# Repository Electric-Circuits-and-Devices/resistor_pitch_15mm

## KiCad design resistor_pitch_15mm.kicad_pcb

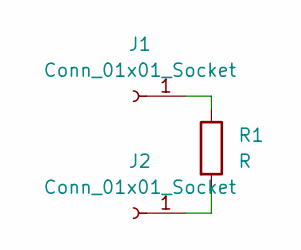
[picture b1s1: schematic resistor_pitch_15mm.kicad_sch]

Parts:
J1, J2: Conn_01x01_Socket; MountingHole_2.5mm_Pad
R1: R; R_Axial_DIN0207_L6.3mm_D2.5mm_P10.16mm_Horizontal

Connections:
unnamed: J1.1, R1.1
unnamed: J2.1, R1.2

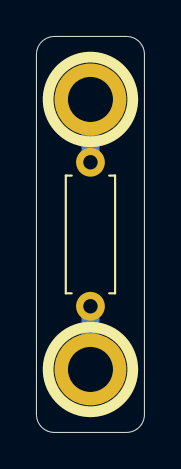
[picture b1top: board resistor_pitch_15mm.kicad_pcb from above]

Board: 2 copper layers, 6.0 x 22.0 mm, 3 parts (0 on the bottom side), 2 nets.
